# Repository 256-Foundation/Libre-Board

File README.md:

# Libre-Board
Open Source Bitcoin Mining Control Board.
Learn more at https://libreboard.org/

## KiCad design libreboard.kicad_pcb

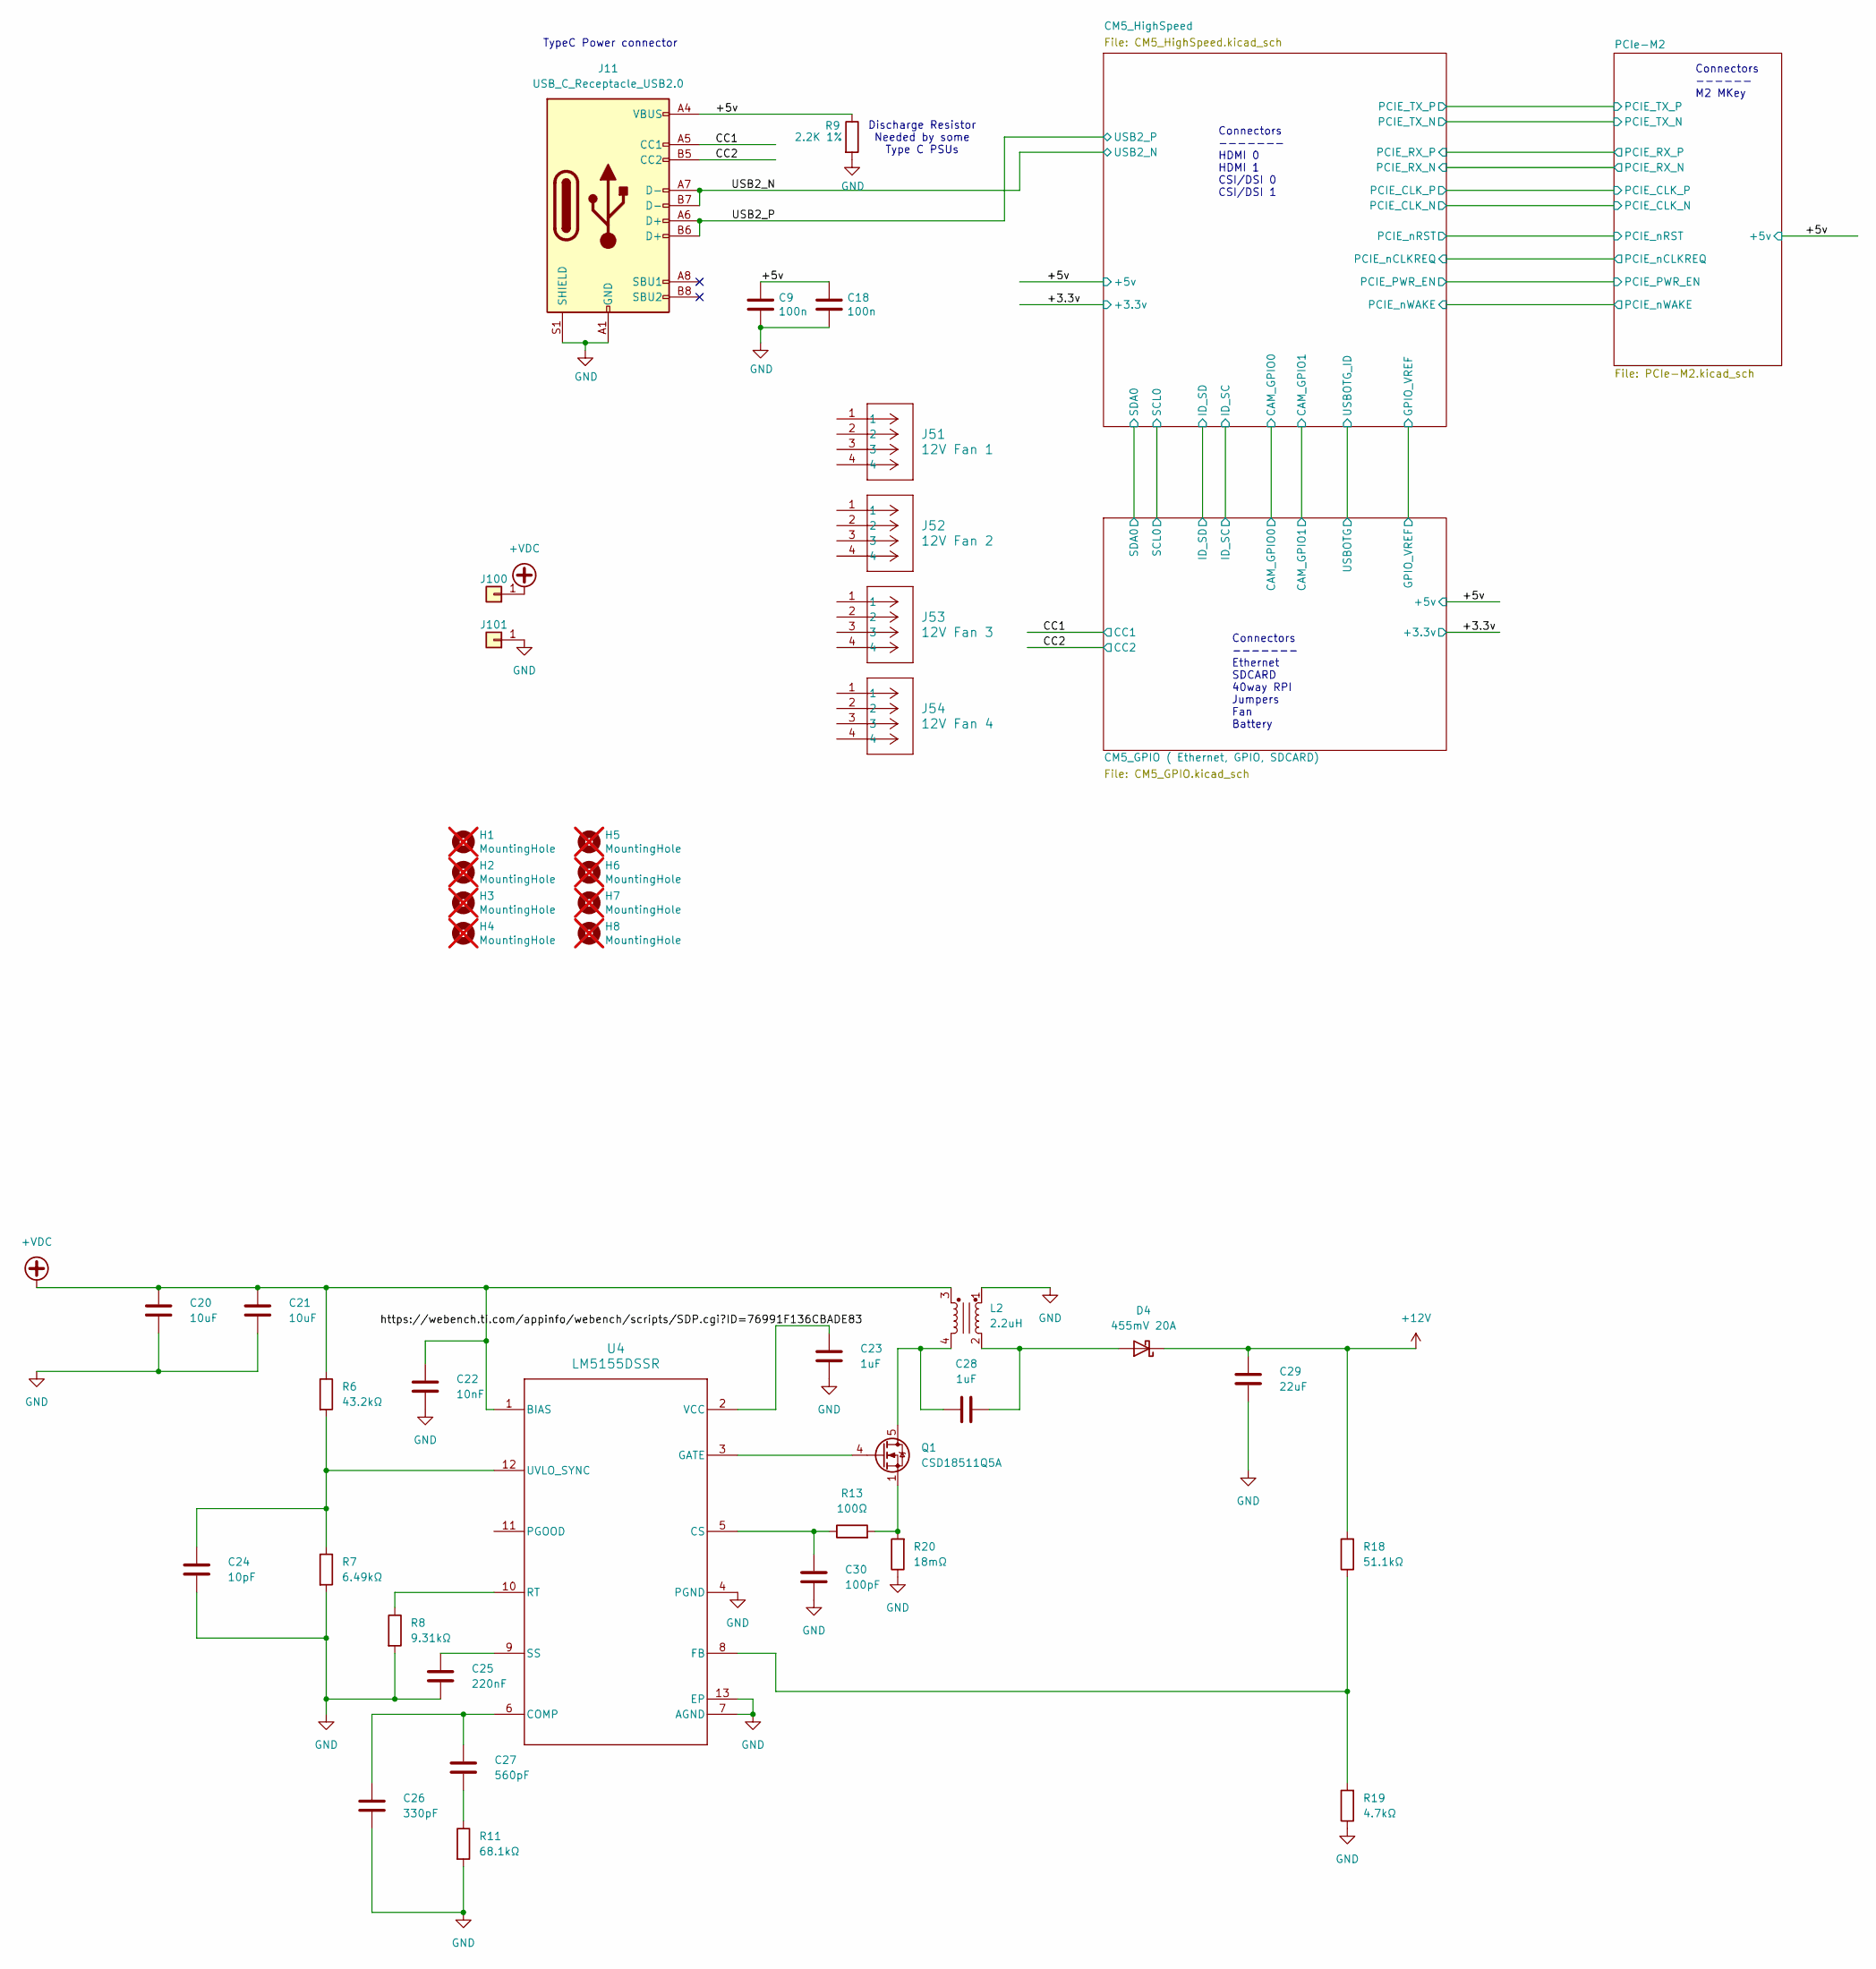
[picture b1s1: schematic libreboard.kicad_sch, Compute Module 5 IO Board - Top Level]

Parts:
C9, C18: 100n; C_0402_1005Metric; Part Description 0.1uF 10% 16V Ceramic Capacitor X7R 040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
C20, C21: 10uF; C_1210_3225Metric
C22: 10nF; C_0603_1608Metric
C23: 1uF; C_0603_1608Metric
C24: 10pF; C_0201_0603Metric
C25: 220nF; C_1812_4532Metric
C26: 330pF; C_0402_1005Metric
C27: 560pF; C_0805_2012Metric
C28: 1uF; C_1206_3216Metric
C29: 22uF; C_1210_3225Metric
C30: 100pF; C_0805_2012Metric
D4: 455mV 20A; TO-220-2_Horizontal_TabDown
H1, H2, H3, H4, H5, H6, H7, H8: MountingHole; MountingHole_2.7mm_M2.5_DIN965; Part Description M2.5 mounting hole; not fitted
J11: USB_C_Receptacle_USB2.0; USB_C_Receptacle_GCT_USB4105-xx-A_16P_TopMnt_Horizontal; Part Description USBC USB2 data and power connector
J51: 12V Fan 1; CONN_SD-47053-001_H10p00_MOL
J52: 12V Fan 2; CONN_SD-47053-001_H10p00_MOL
J53: 12V Fan 3; CONN_SD-47053-001_H10p00_MOL
J54: 12V Fan 4; CONN_SD-47053-001_H10p00_MOL
J100, J101: Screw Terminal; 7770-screw-terminal; PARTNO 36-7770
L2: 2.2uH; L_Bourns_SRF1260
Q1: CSD18511Q5A; VSONP-8-1EP_5x6_P1.27mm; PARTNO CSD18511Q5A
R6: 43.2kΩ; R_0603_1608Metric
R7: 6.49kΩ; R_0603_1608Metric
R8: 9.31kΩ; R_0603_1608Metric
R9: 2.2K 1%; R_0402_1005Metric; Part Description Resistor 2.2K M1005 1% 63mW
R11: 68.1kΩ; R_0603_1608Metric
R13: 100Ω; R_0603_1608Metric
R18: 51.1kΩ; R_0603_1608Metric
R19: 4.7kΩ; R_0603_1608Metric
R20: 18mΩ; R_0612_1632Metric
U4: LM5155DSSR; DSS0012B

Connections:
+12V: C29.2, D4.1 (K), R18.2
+VDC: C20.2, C21.2, C22.2, J100.1, L2.3, R6.1, U4.1 (BIAS)
/+5v: C9.1, C18.1, J11.A4 (VBUS), J11.A9 (VBUS), J11.B4 (VBUS), J11.B9 (VBUS), R9.1; also elsewhere on the board
/CC1: J11.A5 (CC1); also elsewhere on the board
/CC2: J11.B5 (CC2); also elsewhere on the board
/USB2_N: J11.A7 (D-), J11.B7 (D-); also elsewhere on the board
/USB2_P: J11.A6 (D+), J11.B6 (D+); also elsewhere on the board
GND: C9.2, C18.2, C20.1, C21.1, C22.1, C23.1, C24.1, C25.1, C26.1, C29.1, C30.1, J11.A1 (GND), J11.A12 (GND), J11.B1 (GND), J11.B12 (GND), J11.S1 (SHIELD), J101.1, L2.1, R7.2, R8.2, R9.2, R11.2, R19.1, R20.1, U4.4 (PGND), U4.7 (AGND), U4.13 (EP); also elsewhere on the board
unnamed: C27.1, R11.1
unnamed: C28.1, L2.4, Q1.5 (D), Q1.6 (D), Q1.7 (D), Q1.8 (D)
unnamed: C28.2, D4.2 (A), L2.2
unnamed: Q1.4 (G), U4.3 (GATE)
unnamed: Q1.1 (S), Q1.2 (S), Q1.3 (S), R13.2, R20.2
unnamed: C26.2, C27.2, U4.6 (COMP)
unnamed: C30.2, R13.1, U4.5 (CS)
unnamed: R18.1, R19.2, U4.8 (FB)
unnamed: R8.1, U4.10 (RT)
unnamed: C25.2, U4.9 (SS)
unnamed: C24.2, R6.2, R7.1, U4.12 (UVLO_SYNC)
unnamed: C23.2, U4.2 (VCC)

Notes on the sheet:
Connectors ------- Ethernet SDCARD 40way RPI Jumpers Fan Battery
Connectors ------ M2 MKey
Discharge Resistor Needed by some Type C PSUs
TypeC Power connector
Connectors ------- HDMI 0 HDMI 1 CSI/DSI 0 CSI/DSI 1

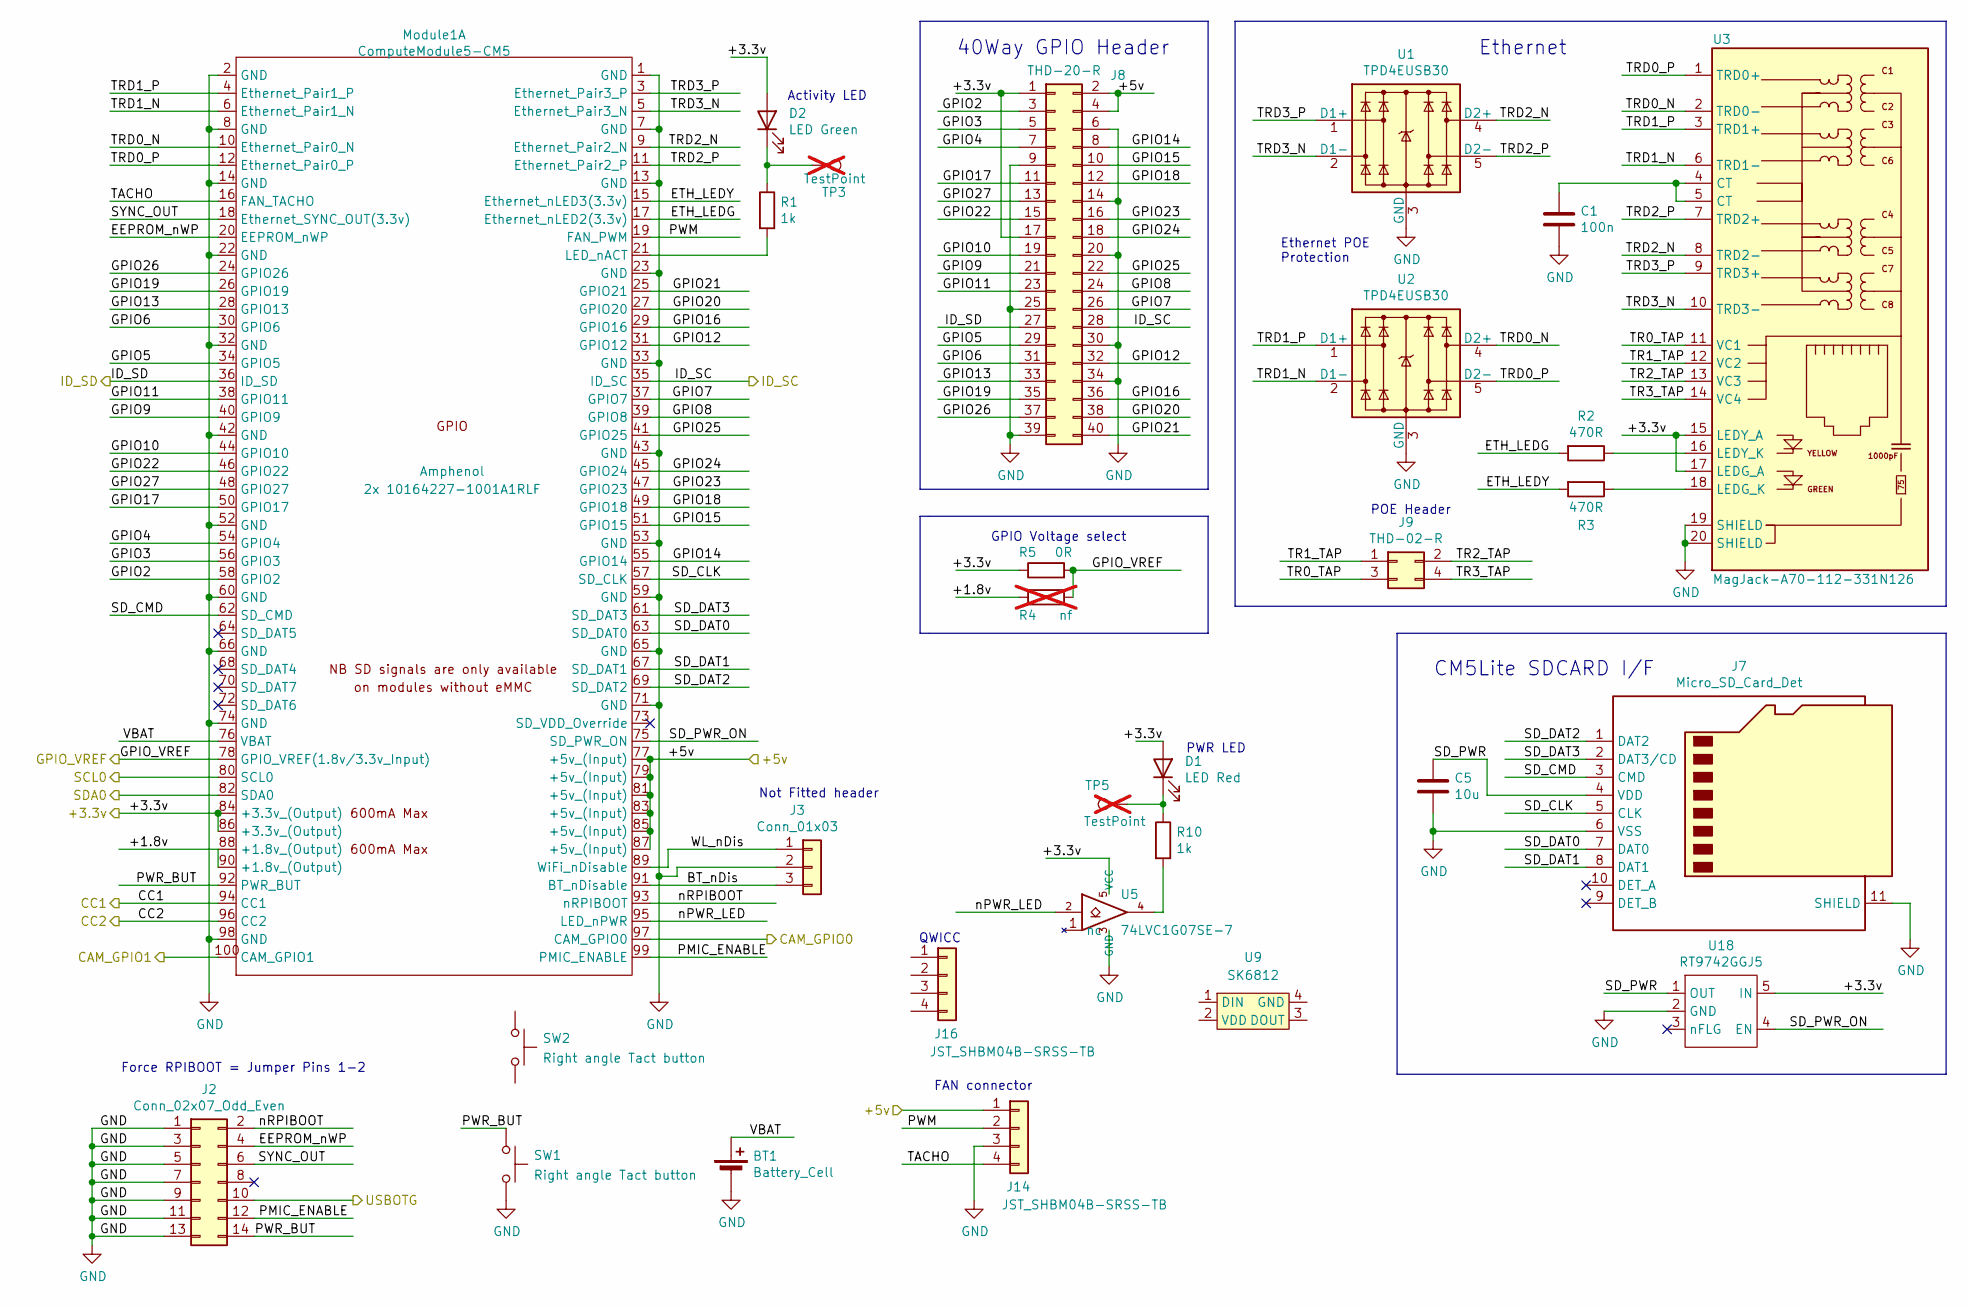
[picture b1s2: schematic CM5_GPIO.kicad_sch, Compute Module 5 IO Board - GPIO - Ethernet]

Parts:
BT1: Battery_Cell; BatteryHolder_Keystone_3034_1x20mm; Part Description Battery Retainer Coin, 20.0mm 1 Cell SM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
C1: 100n; C_0402_1005Metric; Part Description 0.1uF 10% 16V Ceramic Capacitor X7R 040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
C5: 10u; C_0805_2012Metric; Part Description 10uF 10% 10V Ceramic Capacitor X7R 0805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
D1: LED Red; LED_0603_1608Metric; Part Description Red 620nm LED Indication - Discrete 2.2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
D2: LED Green; LED_0603_1608Metric; Part Description Green 572nm LED Indication - Discrete 2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
J2: Conn_02x07_Odd_Even; PinHeader_2x07_P2.54mm_Vertical; Part Description PinHeader_2x07_P2.54mm_Vertical
J3: Conn_01x03; PinHeader_1x03_P2.54mm_Vertical; Part Description 3pin 0.1" connector
J7: Micro_SD_Card_Det; SDCARD_MOLEX_503398-1892; Part Description 9 (8 + 1) Position Card Connector micro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
J8: THD-20-R; PinHeader_2x20_P2.54mm_Vertical; Part Description PinHeader_2x20_P2.54mm_Vertical
J9: THD-02-R; PinHeader_2x02_P2.54mm_Vertical; Part Description PinHeader_2x02_P2.54mm_Vertical
J14, J16: JST_SHBM04B-SRSS-TB; JST_SH_BM04B-SRSS-TB_1x04-1MP_P1.00mm_Vertical; Part Description 4 pin vertical 1mm pitch connector
Module1: ComputeModule5-CM5; Raspberry-Pi-5-Compute-Module; Part Description 100 Position Connector Receptacle, Cent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
R1, R10: 1k; R_0402_1005Metric; Part Description Resistor 1K M1005 1% 63mW
R2, R3: 470R; R_0402_1005Metric; Part Description Resistor 470R M1005 1% 63mW
R4: nf; R_0805_2012Metric_Pad1.20x1.40mm_HandSolder; not fitted
R5: 0R; R_0805_2012Metric_Pad1.20x1.40mm_HandSolder; Part Description Resistor 0R M2012 5%
SW1, SW2: Right angle Tact button; SW_Tactile_SPST_Angled_PTS645Vx58-2LFS; Part Description Right angle through hole Tact switch
TP3, TP5: TestPoint; TestPoint_Pad_2.0x2.0mm; Part Description Test point; not fitted
U1, U2: TPD4EUSB30; USON-10_2.5x1.0mm_P0.5mm; Part Description Quad TVS diode for high speed signals (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
U3: MagJack-A70-112-331N126; TRJG0926HENL; Part Description Gigabit Ethernet Magjack
U5: 74LVC1G07SE-7; SOT-353_SC-70-5; Part Description Buffer, Non-Inverting 1 Element 1 Bit p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
U9: SK6812; LED-SMD_4P-L4.0-W1.6-L; LCSC C2890037
U18: RT9742GGJ5; SOT-23-5; Part Description Power Switch/Driver 1:1 N-Channel 1A TS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

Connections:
/+3.3v: D1.2 (A), D2.2 (A), J8.1, J8.17, Module1.84 (+3.3v_(Output)), Module1.86 (+3.3v_(Output)), R5.1, U3.15 (LEDY_A), U3.17 (LEDG_A), U5.5 (VCC), U18.5 (IN); also elsewhere on the board
/+5v: J8.2, J8.4, J14.1, Module1.77 (+5v_(Input)), Module1.79 (+5v_(Input)), Module1.81 (+5v_(Input)), Module1.83 (+5v_(Input)), Module1.85 (+5v_(Input)), Module1.87 (+5v_(Input)); also elsewhere on the board
/CC1: Module1.94 (CC1); also elsewhere on the board
/CC2: Module1.96 (CC2); also elsewhere on the board
/CM5_GPIO ( Ethernet, GPIO, SDCARD)/+1.8v: Module1.88 (+1.8v_(Output)), Module1.90 (+1.8v_(Output)), R4.1
/CM5_GPIO ( Ethernet, GPIO, SDCARD)/BT_nDis: J3.3, Module1.91 (BT_nDisable)
/CM5_GPIO ( Ethernet, GPIO, SDCARD)/CAM_GPIO0: Module1.97 (CAM_GPIO0); also elsewhere on the board
/CM5_GPIO ( Ethernet, GPIO, SDCARD)/CAM_GPIO1: Module1.100 (CAM_GPIO1); also elsewhere on the board
/CM5_GPIO ( Ethernet, GPIO, SDCARD)/EEPROM_nWP: J2.4, Module1.20 (EEPROM_nWP)
/CM5_GPIO ( Ethernet, GPIO, SDCARD)/ETH_LEDG: Module1.17 (Ethernet_nLED2(3.3v)), R2.2
/CM5_GPIO ( Ethernet, GPIO, SDCARD)/ETH_LEDY: Module1.15 (Ethernet_nLED3(3.3v)), R3.2
/CM5_GPIO ( Ethernet, GPIO, SDCARD)/GPIO2: J8.3, Module1.58 (GPIO2)
/CM5_GPIO ( Ethernet, GPIO, SDCARD)/GPIO3: J8.5, Module1.56 (GPIO3)
/CM5_GPIO ( Ethernet, GPIO, SDCARD)/GPIO4: J8.7, Module1.54 (GPIO4)
/CM5_GPIO ( Ethernet, GPIO, SDCARD)/GPIO5: J8.29, Module1.34 (GPIO5)
/CM5_GPIO ( Ethernet, GPIO, SDCARD)/GPIO6: J8.31, Module1.30 (GPIO6)
/CM5_GPIO ( Ethernet, GPIO, SDCARD)/GPIO7: J8.26, Module1.37 (GPIO7)
/CM5_GPIO ( Ethernet, GPIO, SDCARD)/GPIO8: J8.24, Module1.39 (GPIO8)
/CM5_GPIO ( Ethernet, GPIO, SDCARD)/GPIO9: J8.21, Module1.40 (GPIO9)
/CM5_GPIO ( Ethernet, GPIO, SDCARD)/GPIO10: J8.19, Module1.44 (GPIO10)
/CM5_GPIO ( Ethernet, GPIO, SDCARD)/GPIO11: J8.23, Module1.38 (GPIO11)
/CM5_GPIO ( Ethernet, GPIO, SDCARD)/GPIO12: J8.32, Module1.31 (GPIO12)
/CM5_GPIO ( Ethernet, GPIO, SDCARD)/GPIO13: J8.33, Module1.28 (GPIO13)
/CM5_GPIO ( Ethernet, GPIO, SDCARD)/GPIO14: J8.8, Module1.55 (GPIO14)
/CM5_GPIO ( Ethernet, GPIO, SDCARD)/GPIO15: J8.10, Module1.51 (GPIO15)
/CM5_GPIO ( Ethernet, GPIO, SDCARD)/GPIO16: J8.36, Module1.29 (GPIO16)
/CM5_GPIO ( Ethernet, GPIO, SDCARD)/GPIO17: J8.11, Module1.50 (GPIO17)
/CM5_GPIO ( Ethernet, GPIO, SDCARD)/GPIO18: J8.12, Module1.49 (GPIO18)
/CM5_GPIO ( Ethernet, GPIO, SDCARD)/GPIO19: J8.35, Module1.26 (GPIO19)
/CM5_GPIO ( Ethernet, GPIO, SDCARD)/GPIO20: J8.38, Module1.27 (GPIO20)
/CM5_GPIO ( Ethernet, GPIO, SDCARD)/GPIO21: J8.40, Module1.25 (GPIO21)
/CM5_GPIO ( Ethernet, GPIO, SDCARD)/GPIO22: J8.15, Module1.46 (GPIO22)
/CM5_GPIO ( Ethernet, GPIO, SDCARD)/GPIO23: J8.16, Module1.47 (GPIO23)
/CM5_GPIO ( Ethernet, GPIO, SDCARD)/GPIO24: J8.18, Module1.45 (GPIO24)
/CM5_GPIO ( Ethernet, GPIO, SDCARD)/GPIO25: J8.22, Module1.41 (GPIO25)
/CM5_GPIO ( Ethernet, GPIO, SDCARD)/GPIO26: J8.37, Module1.24 (GPIO26)
/CM5_GPIO ( Ethernet, GPIO, SDCARD)/GPIO27: J8.13, Module1.48 (GPIO27)
/CM5_GPIO ( Ethernet, GPIO, SDCARD)/GPIO_VREF: Module1.78 (GPIO_VREF(1.8v/3.3v_Input)), R4.2, R5.2
/CM5_GPIO ( Ethernet, GPIO, SDCARD)/ID_SC: J8.28, Module1.35 (ID_SC)
/CM5_GPIO ( Ethernet, GPIO, SDCARD)/ID_SD: J8.27, Module1.36 (ID_SD)
/CM5_GPIO ( Ethernet, GPIO, SDCARD)/PMIC_ENABLE: J2.12, Module1.99 (PMIC_ENABLE)
/CM5_GPIO ( Ethernet, GPIO, SDCARD)/PWM: J14.2, Module1.19 (FAN_PWM)
/CM5_GPIO ( Ethernet, GPIO, SDCARD)/PWR_BUT: J2.14, Module1.92 (PWR_BUT), SW1.1
/CM5_GPIO ( Ethernet, GPIO, SDCARD)/SD_CLK: J7.5 (CLK), Module1.57 (SD_CLK)
/CM5_GPIO ( Ethernet, GPIO, SDCARD)/SD_CMD: J7.3 (CMD), Module1.62 (SD_CMD)
/CM5_GPIO ( Ethernet, GPIO, SDCARD)/SD_DAT0: J7.7 (DAT0), Module1.63 (SD_DAT0)
/CM5_GPIO ( Ethernet, GPIO, SDCARD)/SD_DAT1: J7.8 (DAT1), Module1.67 (SD_DAT1)
/CM5_GPIO ( Ethernet, GPIO, SDCARD)/SD_DAT2: J7.1 (DAT2), Module1.69 (SD_DAT2)
/CM5_GPIO ( Ethernet, GPIO, SDCARD)/SD_DAT3: J7.2 (DAT3/CD), Module1.61 (SD_DAT3)
/CM5_GPIO ( Ethernet, GPIO, SDCARD)/SD_PWR: C5.1, J7.4 (VDD), U18.1 (OUT)
/CM5_GPIO ( Ethernet, GPIO, SDCARD)/SD_PWR_ON: Module1.75 (SD_PWR_ON), U18.4 (EN)
/CM5_GPIO ( Ethernet, GPIO, SDCARD)/SYNC_OUT: J2.6, Module1.18 (Ethernet_SYNC_OUT(3.3v))
/CM5_GPIO ( Ethernet, GPIO, SDCARD)/TACHO: J14.4, Module1.16 (FAN_TACHO)
/CM5_GPIO ( Ethernet, GPIO, SDCARD)/TR0_TAP: J9.3, U3.11 (VC1)
/CM5_GPIO ( Ethernet, GPIO, SDCARD)/TR1_TAP: J9.1, U3.12 (VC2)
/CM5_GPIO ( Ethernet, GPIO, SDCARD)/TR2_TAP: J9.2, U3.13 (VC3)
/CM5_GPIO ( Ethernet, GPIO, SDCARD)/TR3_TAP: J9.4, U3.14 (VC4)
/CM5_GPIO ( Ethernet, GPIO, SDCARD)/TRD0_N: Module1.10 (Ethernet_Pair0_N), U2.4 (D2+), U2.7, U3.2 (TRD0-)
/CM5_GPIO ( Ethernet, GPIO, SDCARD)/TRD0_P: Module1.12 (Ethernet_Pair0_P), U2.5 (D2-), U2.6, U3.1 (TRD0+)
/CM5_GPIO ( Ethernet, GPIO, SDCARD)/TRD1_N: Module1.6 (Ethernet_Pair1_N), U2.2 (D1-), U2.9, U3.6 (TRD1-)
/CM5_GPIO ( Ethernet, GPIO, SDCARD)/TRD1_P: Module1.4 (Ethernet_Pair1_P), U2.1 (D1+), U2.10, U3.3 (TRD1+)
/CM5_GPIO ( Ethernet, GPIO, SDCARD)/TRD2_N: Module1.9 (Ethernet_Pair2_N), U1.4 (D2+), U1.7, U3.8 (TRD2-)
/CM5_GPIO ( Ethernet, GPIO, SDCARD)/TRD2_P: Module1.11 (Ethernet_Pair2_P), U1.5 (D2-), U1.6, U3.7 (TRD2+)
/CM5_GPIO ( Ethernet, GPIO, SDCARD)/TRD3_N: Module1.5 (Ethernet_Pair3_N), U1.2 (D1-), U1.9, U3.10 (TRD3-)
/CM5_GPIO ( Ethernet, GPIO, SDCARD)/TRD3_P: Module1.3 (Ethernet_Pair3_P), U1.1 (D1+), U1.10, U3.9 (TRD3+)
/CM5_GPIO ( Ethernet, GPIO, SDCARD)/USBOTG: J2.10; also elsewhere on the board
/CM5_GPIO ( Ethernet, GPIO, SDCARD)/VBAT: BT1.1 (+), Module1.76 (VBAT)
/CM5_GPIO ( Ethernet, GPIO, SDCARD)/WL_nDis: J3.1, Module1.89 (WiFi_nDisable)
/CM5_GPIO ( Ethernet, GPIO, SDCARD)/nPWR_LED: Module1.95 (LED_nPWR), U5.2
/CM5_GPIO ( Ethernet, GPIO, SDCARD)/nRPIBOOT: J2.2, Module1.93 (nRPIBOOT)
/CM5_HighSpeed/SCL0: Module1.80 (SCL0); also elsewhere on the board
/CM5_HighSpeed/SDA0: Module1.82 (SDA0); also elsewhere on the board
GND: BT1.2 (-), C1.2, C5.2, J2.1, J2.3, J2.5, J2.7, J2.9, J2.11, J2.13, J3.2, J7.6 (VSS), J7.11 (SHIELD), J8.6, J8.9, J8.14, J8.20, J8.25, J8.30, J8.34, J8.39, J14.3, Module1.1 (GND), Module1.2 (GND), Module1.7 (GND), Module1.8 (GND), Module1.13 (GND), Module1.14 (GND), Module1.22 (GND), Module1.23 (GND), Module1.32 (GND), Module1.33 (GND), Module1.42 (GND), Module1.43 (GND), Module1.52 (GND), Module1.53 (GND), Module1.59 (GND), Module1.60 (GND), Module1.65 (GND), Module1.66 (GND), Module1.71 (GND), Module1.74 (GND), Module1.98 (GND), SW1.2, U1.3 (GND), U1.8 (GND), U2.3 (GND), U2.8 (GND), U3.19 (SHIELD), U3.20 (SHIELD), U5.3 (GND), U18.2 (GND); also elsewhere on the board
unnamed: C1.1, U3.4 (CT), U3.5 (CT)
unnamed: D1.1 (K), R10.1, TP5.1
unnamed: D2.1 (K), R1.1, TP3.1
unnamed: Module1.21 (LED_nACT), R1.2
unnamed: R10.2, U5.4
unnamed: R3.1, U3.18 (LEDG_K)
unnamed: R2.1, U3.16 (LEDY_K)

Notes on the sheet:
QWICC
40Way GPIO Header
Activity LED
FAN connector
Ethernet POE Protection
GPIO Voltage select
Not Fitted header
POE Header
Force RPIBOOT = Jumper Pins 1-2
PWR LED
Ethernet
CM5Lite SDCARD I/F

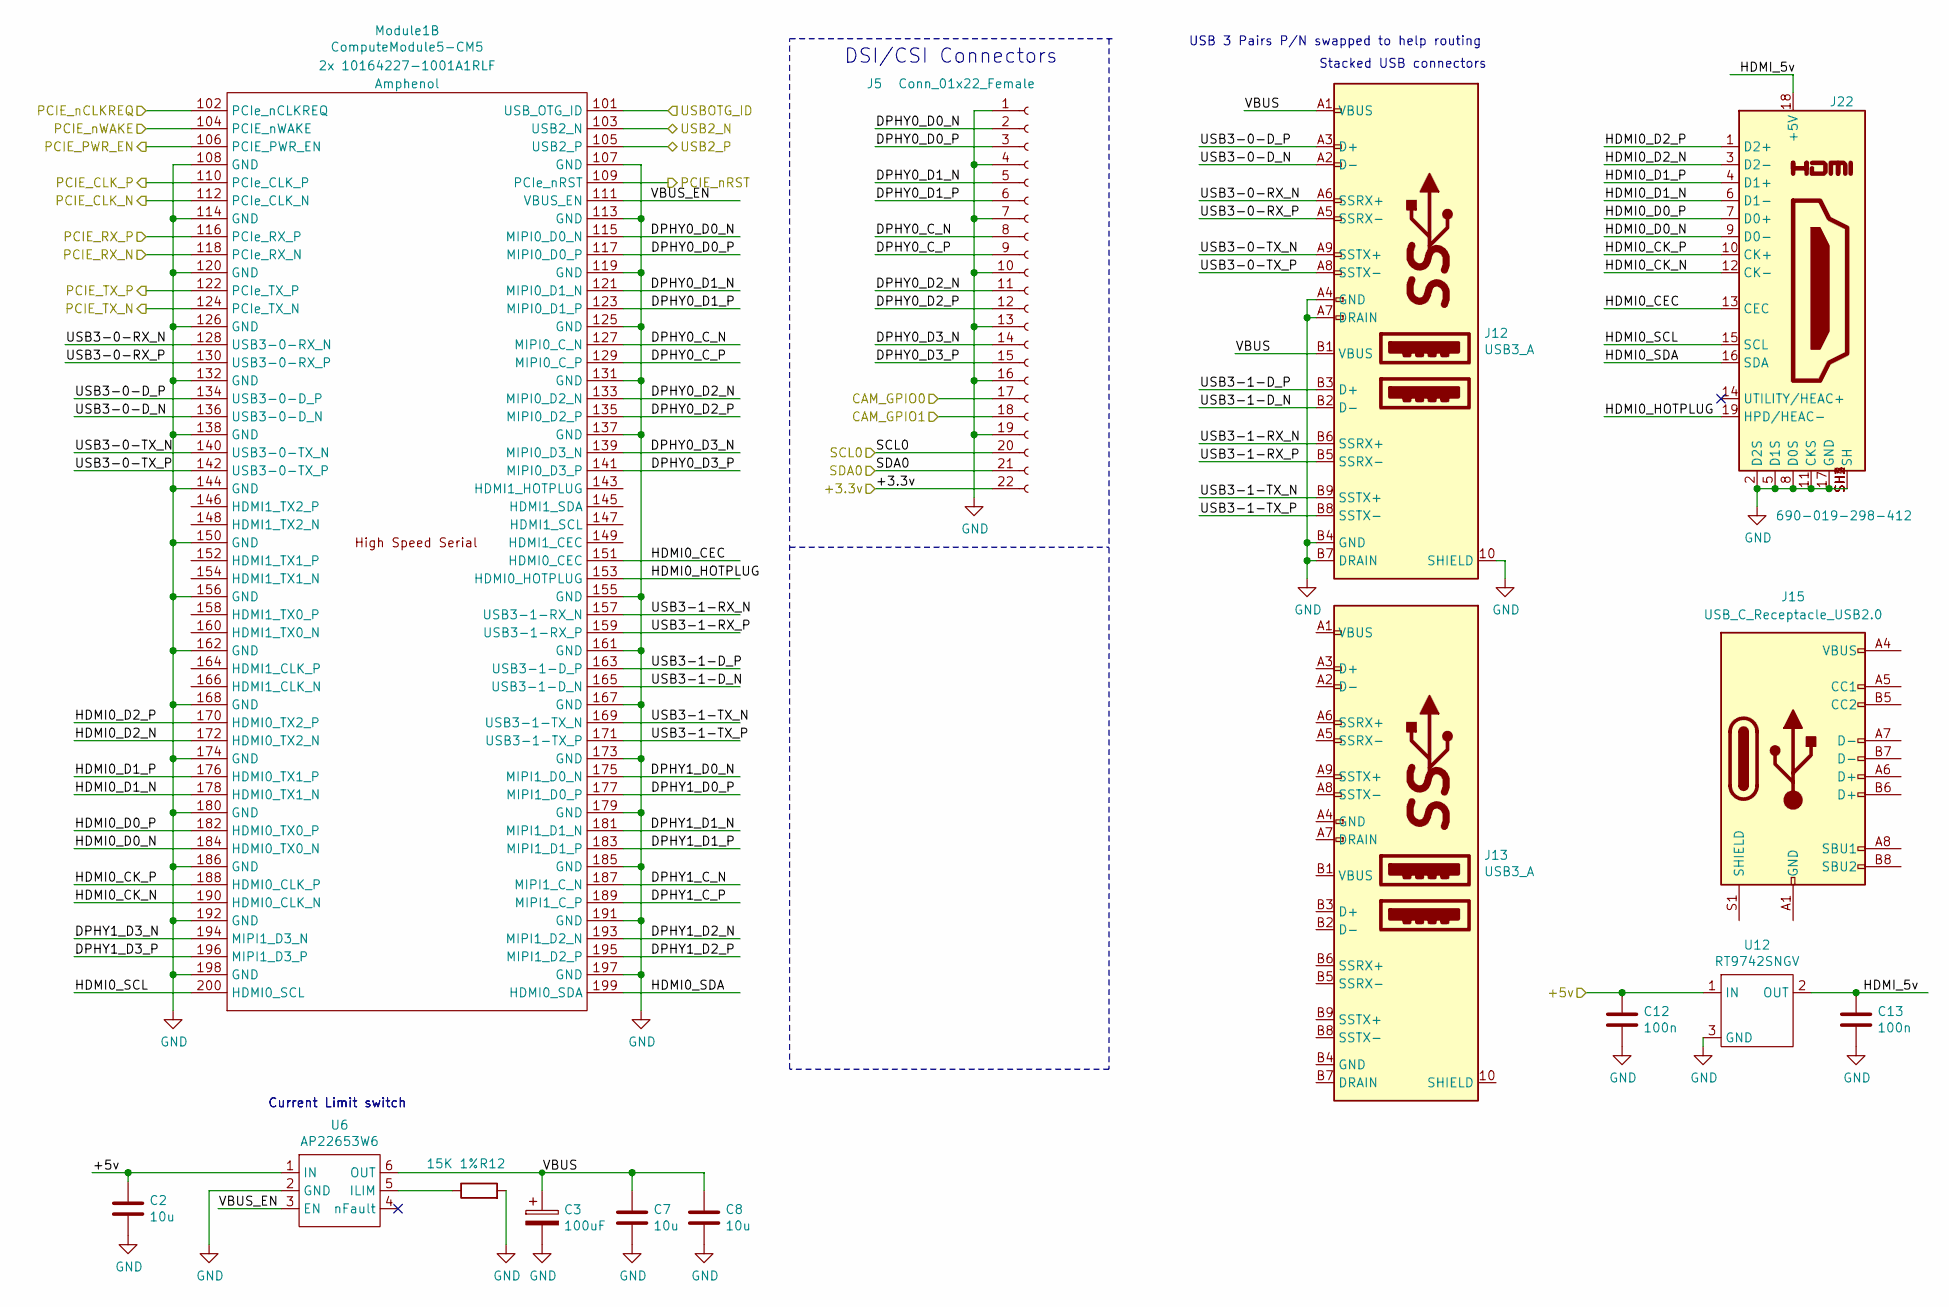
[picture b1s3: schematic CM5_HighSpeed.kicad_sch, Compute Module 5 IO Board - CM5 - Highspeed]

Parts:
C2, C7, C8: 10u; C_0805_2012Metric; Part Description 10uF 10% 10V Ceramic Capacitor X7R 0805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
C3: 100uF; CP_EIA-7343-31_Kemet-D; Part Description Capacitor, SP-Cap, 100u, 6.3V, 15mR ESR
C12, C13: 100n; C_0402_1005Metric; Part Description 0.1uF 10% 16V Ceramic Capacitor X7R 040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
J5: Conn_01x22_Female; Hirose_FH12-22S-0.5SH_1x22-1MP_P0.50mm_Horizontal; Part Description 22 Position FFC, FPC Connector Contacts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
J12, J13: USB3_A; MTCONN_UBAF30-D2011; Part Description Dual USB 3 connector
J15: USB_C_Receptacle_USB2.0; USB_C_Receptacle_GCT_USB4105-xx-A_16P_TopMnt_Horizontal; Part Description USBC USB2 data and power connector
J22: 690-019-298-412; EDAC 690-019-298-412; Part Description HDMI Connector, Right Angle, 19 Contact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
Module1: ComputeModule5-CM5; Raspberry-Pi-5-Compute-Module; Part Description 100 Position Connector Receptacle, Cent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
R12: 15K 1%; R_0402_1005Metric; Part Description Resistor 15K M1005 1% 63mW
U6: AP22653W6; SOT-23-6; Part Description Power Switch/Driver 1:1 P-Channel 2.1A 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
U12: RT9742SNGV; TSOT-23_HandSoldering; Part Description Power Switch/Driver 1:1 N-Channel 500mA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

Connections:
/+3.3v: J5.22; also elsewhere on the board
/+5v: C2.1, C12.1, U6.1 (IN), U12.1 (IN); also elsewhere on the board
/CM5_GPIO ( Ethernet, GPIO, SDCARD)/CAM_GPIO0: J5.17; also elsewhere on the board
/CM5_GPIO ( Ethernet, GPIO, SDCARD)/CAM_GPIO1: J5.18; also elsewhere on the board
/CM5_GPIO ( Ethernet, GPIO, SDCARD)/USBOTG: Module1.101 (USB_OTG_ID); also elsewhere on the board
/CM5_HighSpeed/DPHY0_C_N: J5.8, Module1.127 (MIPI0_C_N)
/CM5_HighSpeed/DPHY0_C_P: J5.9, Module1.129 (MIPI0_C_P)
/CM5_HighSpeed/DPHY0_D0_N: J5.2, Module1.115 (MIPI0_D0_N)
/CM5_HighSpeed/DPHY0_D0_P: J5.3, Module1.117 (MIPI0_D0_P)
/CM5_HighSpeed/DPHY0_D1_N: J5.5, Module1.121 (MIPI0_D1_N)
/CM5_HighSpeed/DPHY0_D1_P: J5.6, Module1.123 (MIPI0_D1_P)
/CM5_HighSpeed/DPHY0_D2_N: J5.11, Module1.133 (MIPI0_D2_N)
/CM5_HighSpeed/DPHY0_D2_P: J5.12, Module1.135 (MIPI0_D2_P)
/CM5_HighSpeed/DPHY0_D3_N: J5.14, Module1.139 (MIPI0_D3_N)
/CM5_HighSpeed/DPHY0_D3_P: J5.15, Module1.141 (MIPI0_D3_P)
/CM5_HighSpeed/DPHY1_C_N: Module1.187 (MIPI1_C_N)
/CM5_HighSpeed/DPHY1_C_P: Module1.189 (MIPI1_C_P)
/CM5_HighSpeed/DPHY1_D0_N: Module1.175 (MIPI1_D0_N)
/CM5_HighSpeed/DPHY1_D0_P: Module1.177 (MIPI1_D0_P)
/CM5_HighSpeed/DPHY1_D1_N: Module1.181 (MIPI1_D1_N)
/CM5_HighSpeed/DPHY1_D1_P: Module1.183 (MIPI1_D1_P)
/CM5_HighSpeed/DPHY1_D2_N: Module1.193 (MIPI1_D2_N)
/CM5_HighSpeed/DPHY1_D2_P: Module1.195 (MIPI1_D2_P)
/CM5_HighSpeed/DPHY1_D3_N: Module1.194 (MIPI1_D3_N)
/CM5_HighSpeed/DPHY1_D3_P: Module1.196 (MIPI1_D3_P)
/CM5_HighSpeed/HDMI0_CEC: J22.13 (CEC), Module1.151 (HDMI0_CEC)
/CM5_HighSpeed/HDMI0_CK_N: J22.12 (CK-), Module1.190 (HDMI0_CLK_N)
/CM5_HighSpeed/HDMI0_CK_P: J22.10 (CK+), Module1.188 (HDMI0_CLK_P)
/CM5_HighSpeed/HDMI0_D0_N: J22.9 (D0-), Module1.184 (HDMI0_TX0_N)
/CM5_HighSpeed/HDMI0_D0_P: J22.7 (D0+), Module1.182 (HDMI0_TX0_P)
/CM5_HighSpeed/HDMI0_D1_N: J22.6 (D1-), Module1.178 (HDMI0_TX1_N)
/CM5_HighSpeed/HDMI0_D1_P: J22.4 (D1+), Module1.176 (HDMI0_TX1_P)
/CM5_HighSpeed/HDMI0_D2_N: J22.3 (D2-), Module1.172 (HDMI0_TX2_N)
/CM5_HighSpeed/HDMI0_D2_P: J22.1 (D2+), Module1.170 (HDMI0_TX2_P)
/CM5_HighSpeed/HDMI0_HOTPLUG: J22.19 (HPD/HEAC-), Module1.153 (HDMI0_HOTPLUG)
/CM5_HighSpeed/HDMI0_SCL: J22.15 (SCL), Module1.200 (HDMI0_SCL)
/CM5_HighSpeed/HDMI0_SDA: J22.16 (SDA), Module1.199 (HDMI0_SDA)
/CM5_HighSpeed/HDMI_5v: C13.1, J22.18 (+5V), U12.2 (OUT)
/CM5_HighSpeed/PCIE_CLK_N: Module1.112 (PCIe_CLK_N); also elsewhere on the board
/CM5_HighSpeed/PCIE_CLK_P: Module1.110 (PCIe_CLK_P); also elsewhere on the board
/CM5_HighSpeed/PCIE_PWR_EN: Module1.106 (PCIE_PWR_EN); also elsewhere on the board
/CM5_HighSpeed/PCIE_RX_N: Module1.118 (PCIe_RX_N); also elsewhere on the board
/CM5_HighSpeed/PCIE_RX_P: Module1.116 (PCIe_RX_P); also elsewhere on the board
/CM5_HighSpeed/PCIE_TX_N: Module1.124 (PCIe_TX_N); also elsewhere on the board
/CM5_HighSpeed/PCIE_TX_P: Module1.122 (PCIe_TX_P); also elsewhere on the board
/CM5_HighSpeed/PCIE_nCLKREQ: Module1.102 (PCIe_nCLKREQ); also elsewhere on the board
/CM5_HighSpeed/PCIE_nRST: Module1.109 (PCIe_nRST); also elsewhere on the board
/CM5_HighSpeed/PCIE_nWAKE: Module1.104 (PCIE_nWAKE); also elsewhere on the board
/CM5_HighSpeed/SCL0: J5.20; also elsewhere on the board
/CM5_HighSpeed/SDA0: J5.21; also elsewhere on the board
/CM5_HighSpeed/USB3-0-D_N: J12.A2 (D-), Module1.136 (USB3-0-D_N)
/CM5_HighSpeed/USB3-0-D_P: J12.A3 (D+), Module1.134 (USB3-0-D_P)
/CM5_HighSpeed/USB3-0-RX_N: J12.A6 (SSRX+), Module1.128 (USB3-0-RX_N)
/CM5_HighSpeed/USB3-0-RX_P: J12.A5 (SSRX-), Module1.130 (USB3-0-RX_P)
/CM5_HighSpeed/USB3-0-TX_N: J12.A9 (SSTX+), Module1.140 (USB3-0-TX_N)
/CM5_HighSpeed/USB3-0-TX_P: J12.A8 (SSTX-), Module1.142 (USB3-0-TX_P)
/CM5_HighSpeed/USB3-1-D_N: J12.B2 (D-), Module1.165 (USB3-1-D_N)
/CM5_HighSpeed/USB3-1-D_P: J12.B3 (D+), Module1.163 (USB3-1-D_P)
/CM5_HighSpeed/USB3-1-RX_N: J12.B6 (SSRX+), Module1.157 (USB3-1-RX_N)
/CM5_HighSpeed/USB3-1-RX_P: J12.B5 (SSRX-), Module1.159 (USB3-1-RX_P)
/CM5_HighSpeed/USB3-1-TX_N: J12.B9 (SSTX+), Module1.169 (USB3-1-TX_N)
/CM5_HighSpeed/USB3-1-TX_P: J12.B8 (SSTX-), Module1.171 (USB3-1-TX_P)
/CM5_HighSpeed/VBUS: C3.1, C7.1, C8.1, J12.A1 (VBUS), J12.B1 (VBUS), U6.6 (OUT)
/CM5_HighSpeed/VBUS_EN: Module1.111 (VBUS_EN), U6.3 (EN)
/USB2_N: Module1.103 (USB2_N); also elsewhere on the board
/USB2_P: Module1.105 (USB2_P); also elsewhere on the board
GND: C2.2, C3.2, C7.2, C8.2, C12.2, C13.2, J5.1, J5.4, J5.7, J5.10, J5.13, J5.16, J5.19, J12.10 (SHIELD), J12.A4 (GND), J12.A7 (DRAIN), J12.B4 (GND), J12.B7 (DRAIN), J22.2 (D2S), J22.5 (D1S), J22.8 (D0S), J22.11 (CKS), J22.17 (GND), J22.SH1 (SH), J22.SH2 (SH), J22.SH3 (SH), J22.SH4 (SH), Module1.107 (GND), Module1.108 (GND), Module1.113 (GND), Module1.114 (GND), Module1.119 (GND), Module1.120 (GND), Module1.125 (GND), Module1.126 (GND), Module1.131 (GND), Module1.132 (GND), Module1.137 (GND), Module1.138 (GND), Module1.144 (GND), Module1.150 (GND), Module1.155 (GND), Module1.156 (GND), Module1.161 (GND), Module1.162 (GND), Module1.167 (GND), Module1.168 (GND), Module1.173 (GND), Module1.174 (GND), Module1.179 (GND), Module1.180 (GND), Module1.185 (GND), Module1.186 (GND), Module1.191 (GND), Module1.192 (GND), Module1.197 (GND), Module1.198 (GND), R12.2, U6.2 (GND), U12.3 (GND); also elsewhere on the board
unnamed: J15.A1 (GND), J15.A12 (GND), J15.B1 (GND), J15.B12 (GND)
unnamed: J15.A4 (VBUS), J15.A9 (VBUS), J15.B4 (VBUS), J15.B9 (VBUS)
unnamed: R12.1, U6.5 (ILIM)

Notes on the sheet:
USB 3 Pairs P/N swapped to help routing
Current Limit switch
DSI/CSI Connectors
Stacked USB connectors

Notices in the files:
CM5_GPIO.kicad_sch:
Copyright © 2024 Raspberry Pi Ltd.
